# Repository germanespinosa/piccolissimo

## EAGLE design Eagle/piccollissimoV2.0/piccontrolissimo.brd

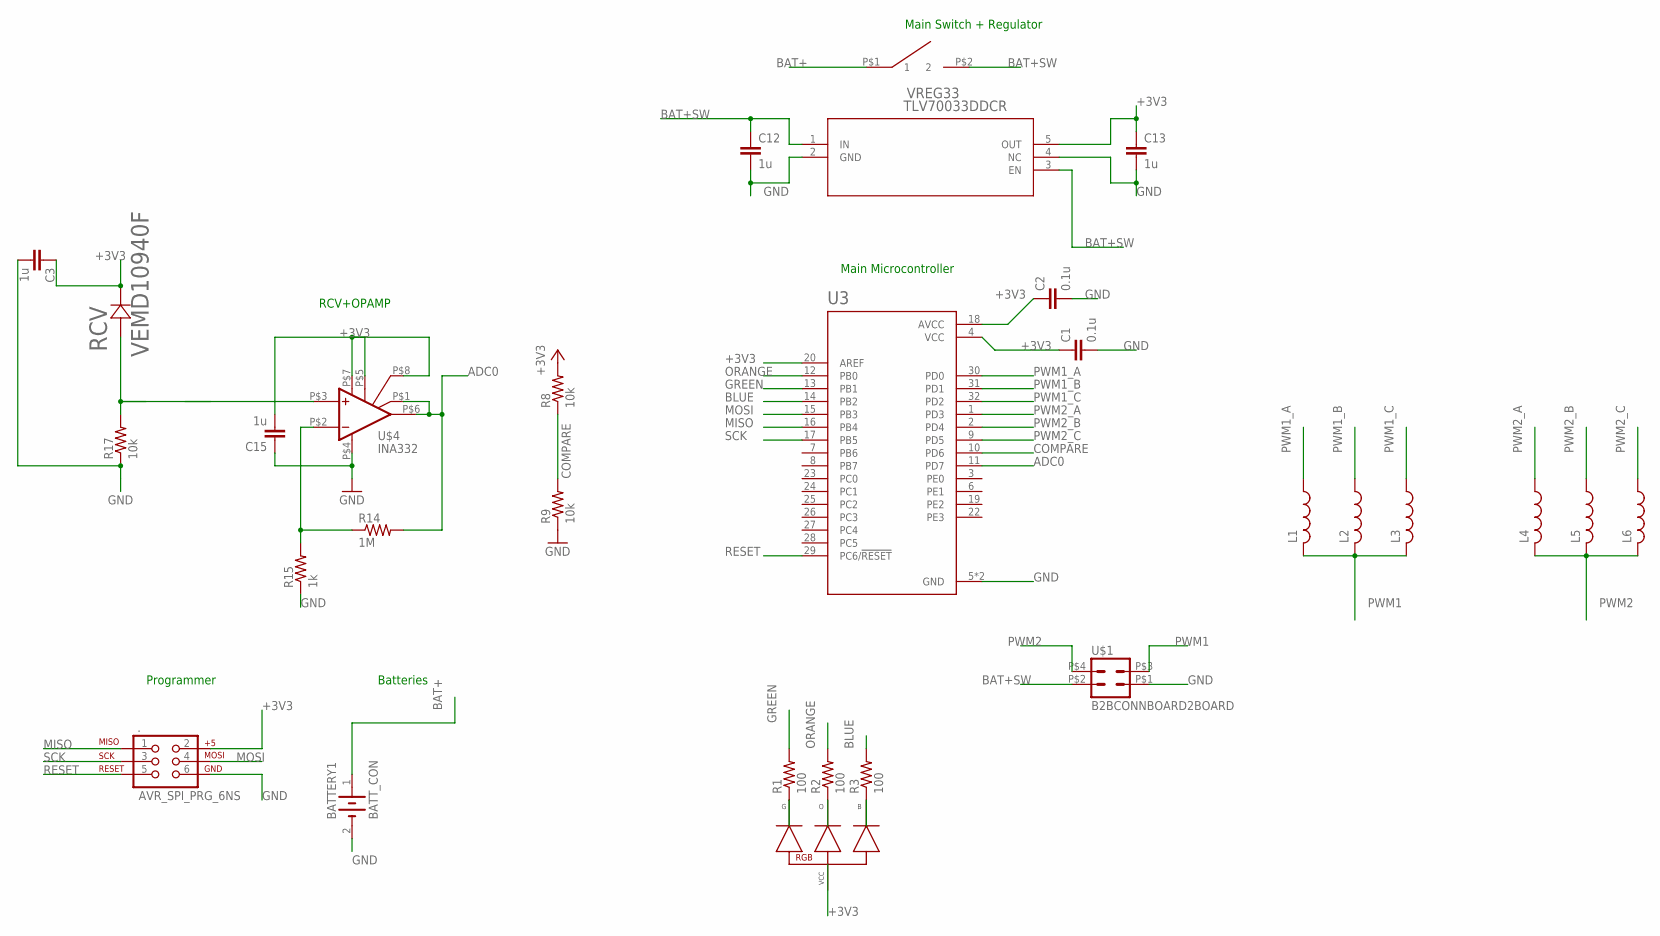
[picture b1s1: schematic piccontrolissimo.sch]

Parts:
.: AVR_SPI_PRG_6NS; 2X3-NS
BATTERY1: BATT_CON; 2X2BATTCON
C1, C2: 0.1u; C0603
C3, C12, C13, C15: 1u; C0603
L1, L2, L3, L4, L5, L6: L-USL0201; L0201
R1, R2, R3: 100; R0603
R8, R9, R17: 10k; R0603
R14: 1M; R0603
R15: 1k; R0603
RCV: VEMD10940F
RGB1: RGBLED
SWITCH: DIP01
U3: ATMEGA328PB-AUR; QFP80P900X900X120-32N
U$1: B2BCONNBOARD2BOARD; B2B
U$4: INA332
VREG33: TLV70033DDCR; DDC5

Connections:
+3V3: ..2, C1.1, C2.1, C3.1, C13.1, C15.2, R8.2, RCV.CA-, RGB1.VCC, U3.4 (VCC), U3.18 (AVCC), U3.20 (AREF), U$4.P$5 (VREF), U$4.P$7 (V+), U$4.P$8 (SHDN), VREG33.5 (OUT)
ADC0: R14.2, U3.11 (PD7), U$4.P$1 (RG), U$4.P$6 (OUT)
BAT+: BATTERY1.1 (+), SWITCH.P$1 (1)
BAT+SW: C12.1, SWITCH.P$2 (2), U$1.P$2 (2), VREG33.1 (IN), VREG33.3 (EN)
BLUE: R3.2, U3.14 (PB2)
BLUER: R3.1, RGB1.BLUE
COMPARE: R8.1, R9.2, U3.10 (PD6)
GND: ..6, BATTERY1.2 (-), C1.2, C2.2, C3.2, C12.2, C13.2, C15.1, R9.1, R15.1, R17.1, U3.5 (GND), U3.21 (GND), U$1.P$1 (1), U$4.P$4 (V-), VREG33.2 (GND), VREG33.4 (NC)
GREEN: R1.2, U3.13 (PB1)
GREENR: R1.1, RGB1.GREEN
MISO: ..1, U3.16 (PB4)
MOSI: ..4, U3.15 (PB3)
unnamed: R14.1, R15.2, U$4.P$2 (-IN)
unnamed: R17.2, RCV.AN+, U$4.P$3 (+IN)
ORANGE: R2.2, U3.12 (PB0)
ORANGER: R2.1, RGB1.ORANGE
PWM1: L1.2, L2.2, L3.2, U$1.P$3 (3)
PWM1_A: L1.1, U3.30 (PD0)
PWM1_B: L2.1, U3.31 (PD1)
PWM1_C: L3.1, U3.32 (PD2)
PWM2: L4.2, L5.2, L6.2, U$1.P$4 (4)
PWM2_A: L4.1, U3.1 (PD3)
PWM2_B: L5.1, U3.2 (PD4)
PWM2_C: L6.1, U3.9 (PD5)
RESET: ..5, U3.29 (PC6/!RESET)
SCK: ..3, U3.17 (PB5)

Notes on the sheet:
Main Switch + Regulator
Batteries
Programmer
RCV+OPAMP
Main Microcontroller

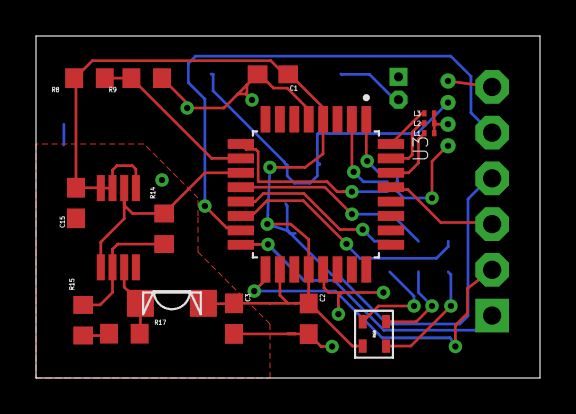
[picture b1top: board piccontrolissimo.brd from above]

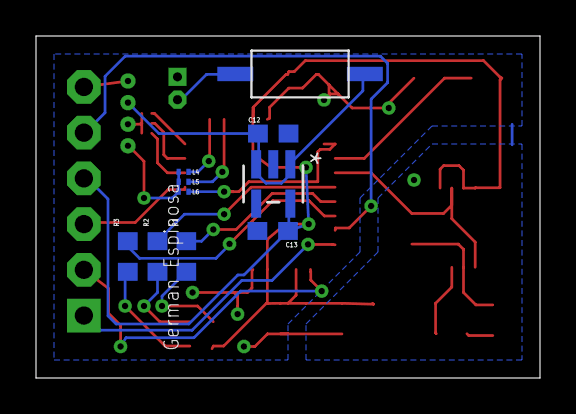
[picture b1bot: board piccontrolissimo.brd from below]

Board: 2 copper layers, 28.0 x 19.0 mm, 29 parts (11 on the bottom side), 26 nets.

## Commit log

2018-09-04 Board
2018-09-04 code
